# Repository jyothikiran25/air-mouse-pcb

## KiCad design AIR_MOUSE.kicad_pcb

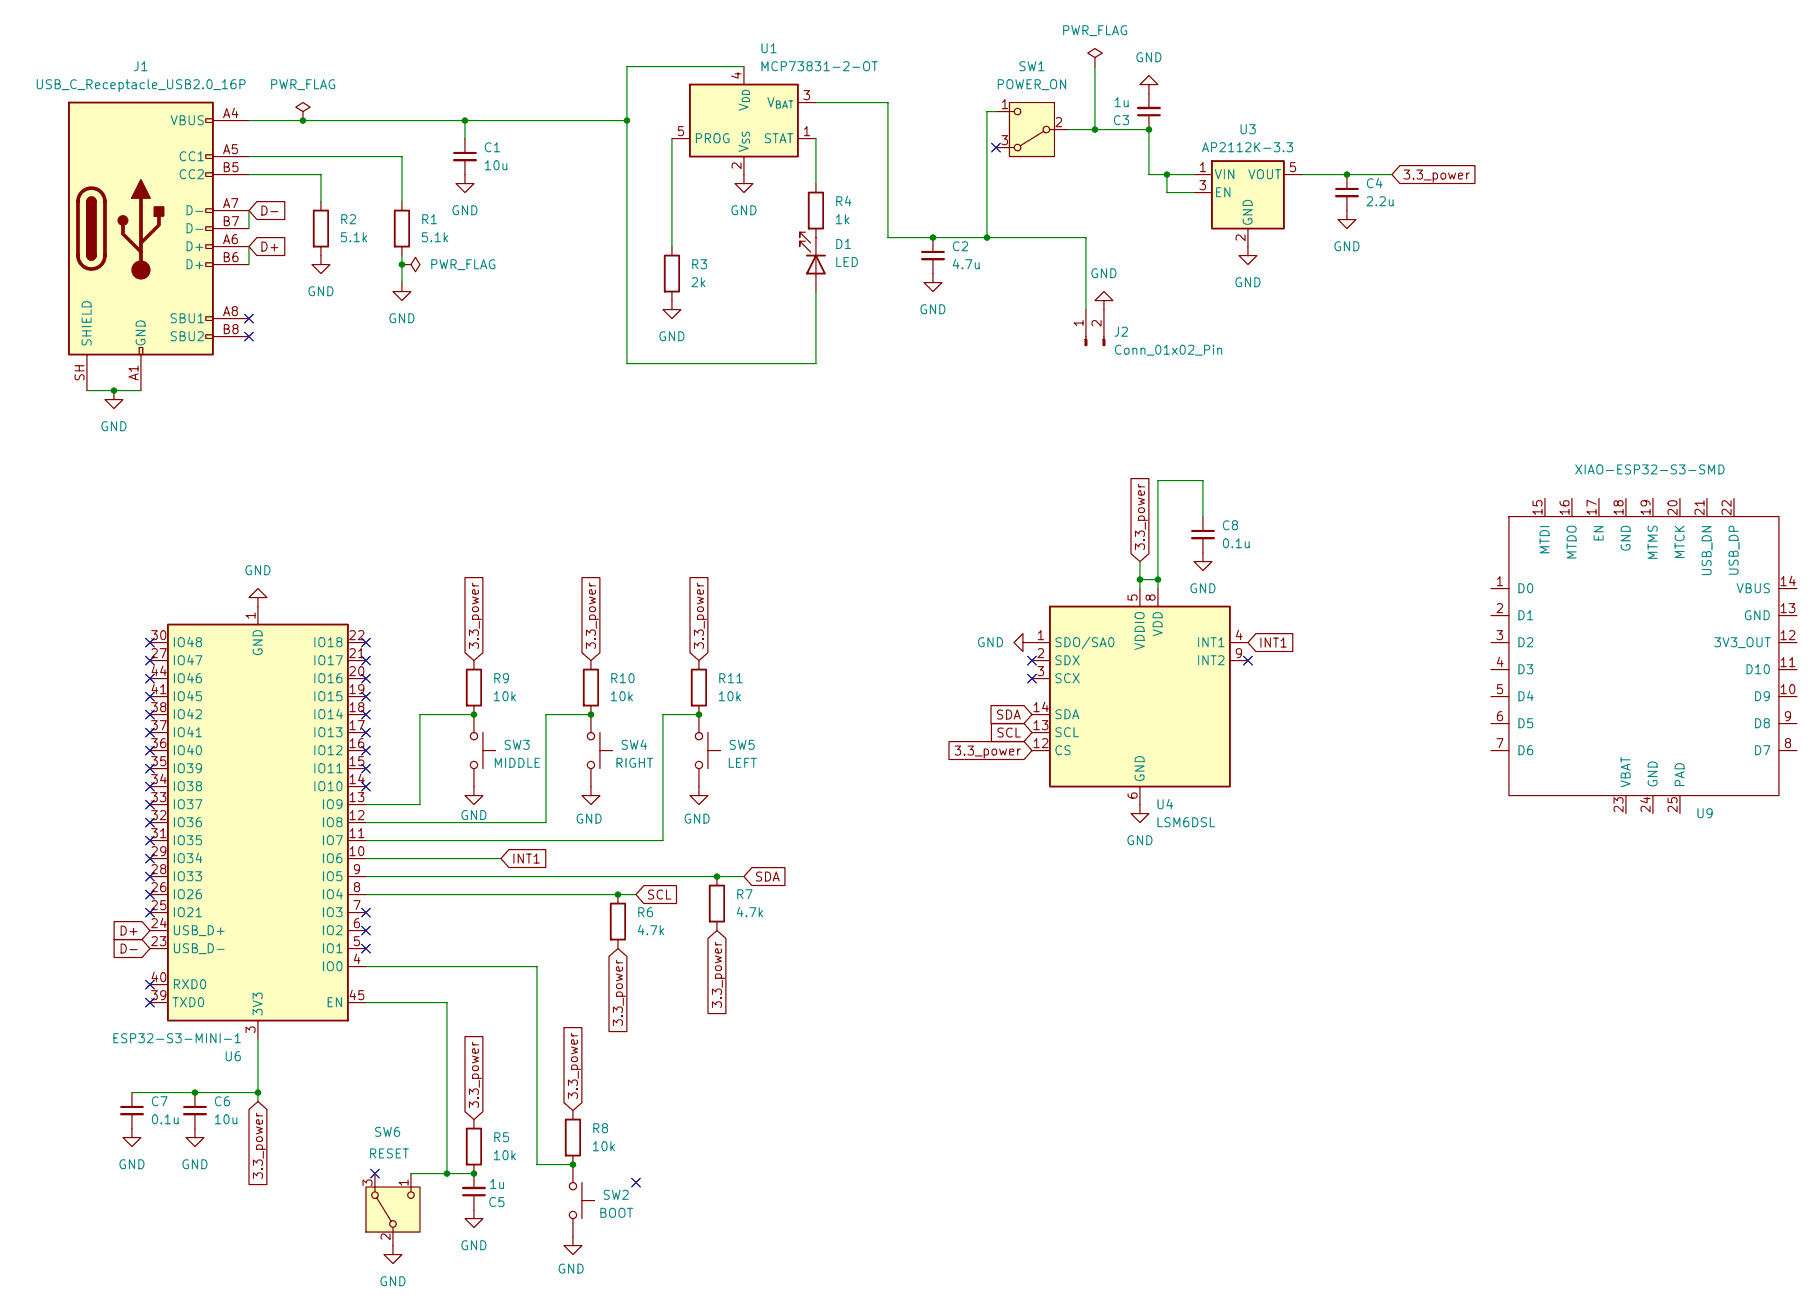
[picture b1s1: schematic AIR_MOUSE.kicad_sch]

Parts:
C1, C6: 10u; C_0805_2012Metric
C2: 4.7u; C_0805_2012Metric
C3, C5: 1u; C_0603_1608Metric
C4: 2.2u; C_0603_1608Metric
C7, C8: 0.1u; C_0603_1608Metric
D1: LED; LED_0603_1608Metric
J1: USB_C_Receptacle_USB2.0_16P; USB_C_Receptacle_HRO_TYPE-C-31-M-12
J2: Conn_01x02_Pin; JST_PH_S2B-PH-K_1x02_P2.00mm_Horizontal
R1, R2: 5.1k; R_0603_1608Metric
R3: 2k; R_0603_1608Metric
R4: 1k; R_0603_1608Metric
R5, R8, R9, R10, R11: 10k; R_0603_1608Metric
R6, R7: 4.7k; R_0603_1608Metric
SW1: POWER_ON; Nidec_Copal_CAS-120A
SW2: BOOT; SW_SPST_TL3342
SW3: MIDDLE; SW_PUSH_6mm_H5mm
SW4: RIGHT; SW_PUSH_6mm_H5mm
SW5: LEFT; SW_PUSH_6mm_H5mm
SW6: RESET; Nidec_Copal_CAS-120A
U1: MCP73831-2-OT; SOT-23-5
U3: AP2112K-3.3; SOT-23-5
U4: LSM6DSL; LGA-14_3x2.5mm_P0.5mm_LayoutBorder3x4y
U6: ESP32-S3-MINI-1; ESP32-S2-MINI-1
U9: XIAO-ESP32-S3-SMD

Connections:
3.3_power: C4.1, C6.1, C7.1, C8.1, R5.1, R6.2, R7.2, R8.1, R9.1, R10.1, R11.1, U3.5 (VOUT), U4.5 (VDDIO), U4.8 (VDD), U4.12 (CS), U6.3 (3V3)
D+: J1.A6 (D+), J1.B6 (D+), U6.24 (USB_D+)
D-: J1.A7 (D-), J1.B7 (D-), U6.23 (USB_D-)
GND: C1.2, C2.2, C3.2, C4.2, C5.1, C6.2, C7.2, C8.2, J1.A1 (GND), J1.A12 (GND), J1.B1 (GND), J1.B12 (GND), J1.SH (SHIELD), J2.2, R1.2, R2.2, R3.2, SW2.2, SW3.2, SW4.2, SW5.2, SW6.2 (B), U1.2 (V_{SS}), U3.2 (GND), U4.1 (SDO/SA0), U4.6 (GND), U4.7 (GND), U6.1 (GND), U6.2 (GND), U6.42 (GND), U6.43 (GND), U6.46 (GND), U6.47 (GND), U6.48 (GND), U6.49 (GND), U6.50 (GND), U6.51 (GND), U6.52 (GND), U6.53 (GND), U6.54 (GND), U6.55 (GND), U6.56 (GND), U6.57 (GND), U6.58 (GND), U6.59 (GND), U6.60 (GND), U6.61 (GND), U6.62 (GND), U6.63 (GND), U6.64 (GND), U6.65 (GND)
INT1: U4.4 (INT1), U6.10 (IO6)
unnamed: C1.1, D1.2 (A), J1.A4 (VBUS), J1.A9 (VBUS), J1.B4 (VBUS), J1.B9 (VBUS), U1.4 (V_{DD})
unnamed: D1.1 (K), R4.2
unnamed: J1.A5 (CC1), R1.1
unnamed: J1.B5 (CC2), R2.1
unnamed: C2.1, J2.1, SW1.1 (C), U1.3 (V_{BAT})
unnamed: C3.1, SW1.2 (B), U3.1 (VIN), U3.3 (EN)
unnamed: C5.2, R5.2, SW6.1 (C), U6.45 (EN)
unnamed: R3.1, U1.5 (PROG)
unnamed: R4.1, U1.1 (STAT)
unnamed: R8.2, SW2.1, U6.4 (IO0)
unnamed: R11.2, SW5.1, U6.11 (IO7)
unnamed: R10.2, SW4.1, U6.12 (IO8)
unnamed: R9.2, SW3.1, U6.13 (IO9)
SCL: R6.1, U4.13 (SCL), U6.8 (IO4)
SDA: R7.1, U4.14 (SDA), U6.9 (IO5)

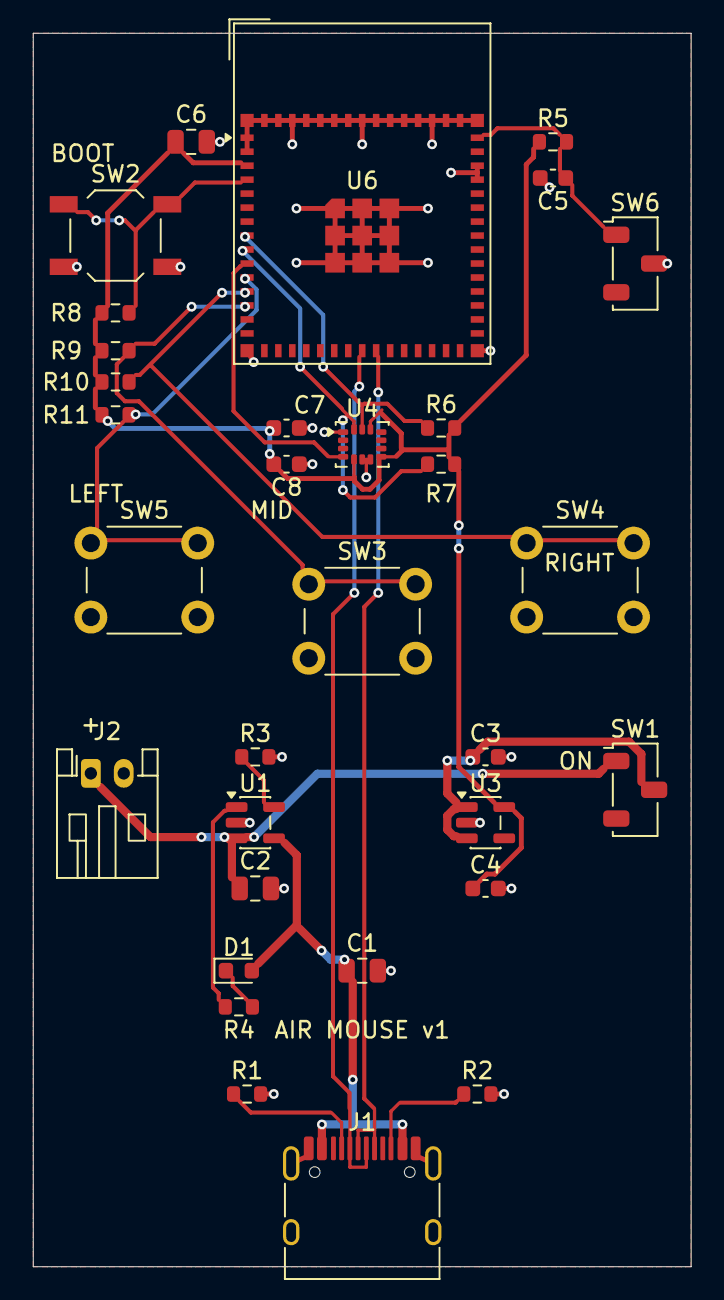
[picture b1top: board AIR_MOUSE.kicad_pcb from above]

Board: 2 copper layers, 40.0 x 75.0 mm, 32 parts (0 on the bottom side), 20 nets.
